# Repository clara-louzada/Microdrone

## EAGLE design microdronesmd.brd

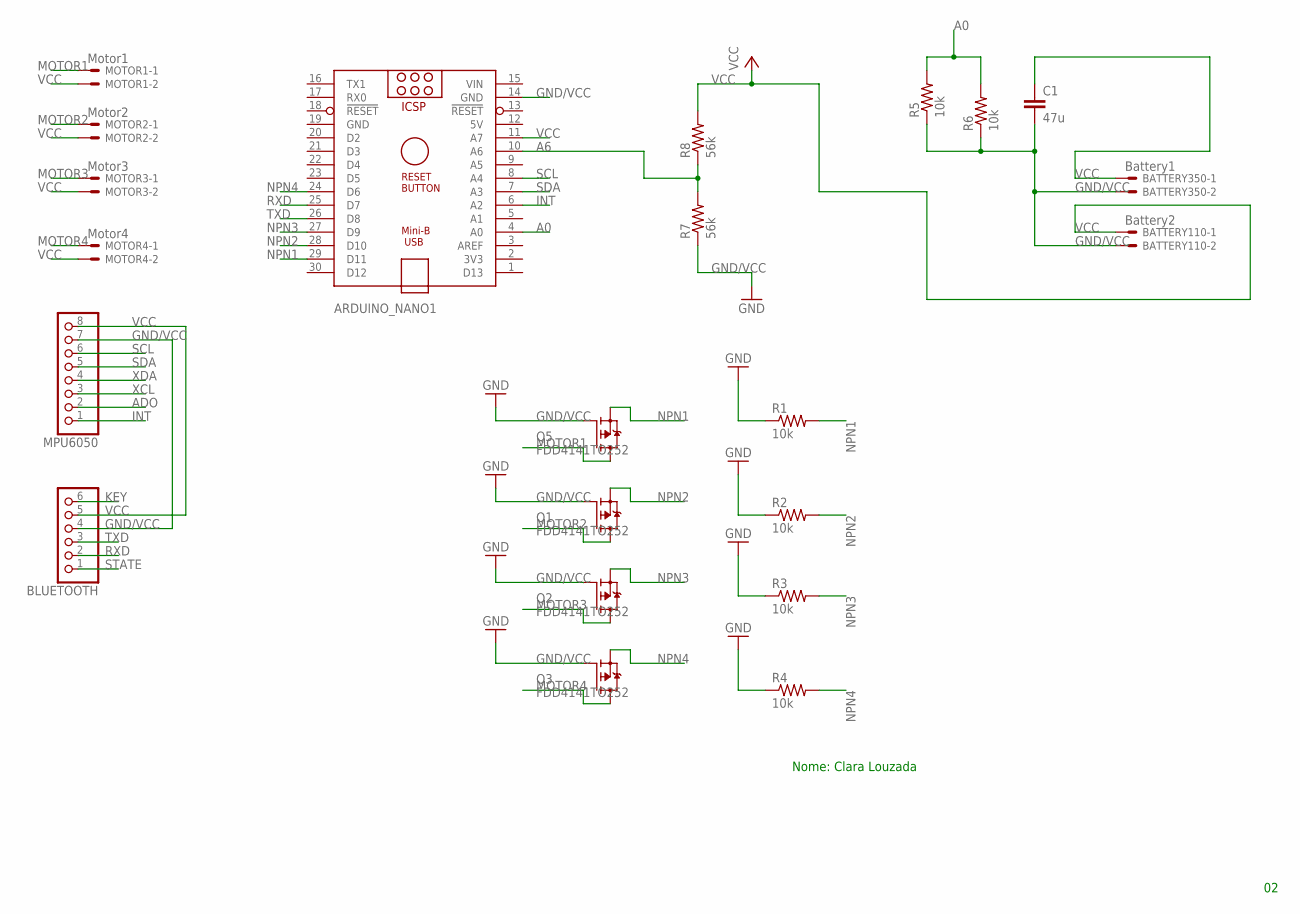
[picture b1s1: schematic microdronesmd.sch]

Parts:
ARDUINO_NANO1: ARDUINO_NANO
BATTERY110: Battery2; JST-XH-02-PACKAGE-LONG-PAD
BATTERY350: Battery1; JST-XH-02-PACKAGE-LONG-PAD
BLUETOOTH: PINHD-1X6; 1X06
C1: 47u; C2.5-3
MOTOR1: Motor1; JST-XH-02-PACKAGE-LONG-PAD
MOTOR2: Motor2; JST-XH-02-PACKAGE-LONG-PAD
MOTOR3: Motor3; JST-XH-02-PACKAGE-LONG-PAD
MOTOR4: Motor4; JST-XH-02-PACKAGE-LONG-PAD
MPU6050: PINHD-1X8; 1X08
Q1, Q2, Q3, Q5: FDD4141TO252; TO252
R1, R2, R3, R4, R5, R6: 10k; 0204/7
R7, R8: 56k; 0204/7

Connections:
5V: ARDUINO_NANO1.12 (5V)
A0: ARDUINO_NANO1.4 (A0), R5.2, R6.2
A6: ARDUINO_NANO1.10 (A6), R7.2, R8.1
ADO: MPU6050.2
GND/VCC: ARDUINO_NANO1.14 (GND), ARDUINO_NANO1.19 (GND), BATTERY110.2, BATTERY350.2, BLUETOOTH.4, C1.2, MPU6050.7, Q1.1 (G), Q2.1 (G), Q3.1 (G), Q5.1 (G), R1.1, R2.1, R3.1, R4.1, R5.1, R6.1, R7.1
INT: ARDUINO_NANO1.6 (A2), MPU6050.1
KEY: BLUETOOTH.6
MOTOR1: MOTOR1.1, Q5.3 (D)
MOTOR2: MOTOR2.1, Q1.3 (D)
MOTOR3: MOTOR3.1, Q2.3 (D)
MOTOR4: MOTOR4.1, Q3.3 (D)
NPN1: ARDUINO_NANO1.29 (D11), Q5.2 (S), R1.2
NPN2: ARDUINO_NANO1.28 (D10), Q1.2 (S), R2.2
NPN3: ARDUINO_NANO1.27 (D9), Q2.2 (S), R3.2
NPN4: ARDUINO_NANO1.24 (D6), Q3.2 (S), R4.2
RXD: ARDUINO_NANO1.25 (D7), BLUETOOTH.2
SCL: ARDUINO_NANO1.8 (A4), MPU6050.6
SDA: ARDUINO_NANO1.7 (A3), MPU6050.5
STATE: BLUETOOTH.1
TXD: ARDUINO_NANO1.26 (D8), BLUETOOTH.3
VCC: ARDUINO_NANO1.11 (A7), BATTERY110.1, BATTERY350.1, BLUETOOTH.5, C1.1, MOTOR1.2, MOTOR2.2, MOTOR3.2, MOTOR4.2, MPU6050.8, R8.2
VIN: ARDUINO_NANO1.15 (VIN)
XCL: MPU6050.3
XDA: MPU6050.4

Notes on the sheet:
Nome: Clara Louzada

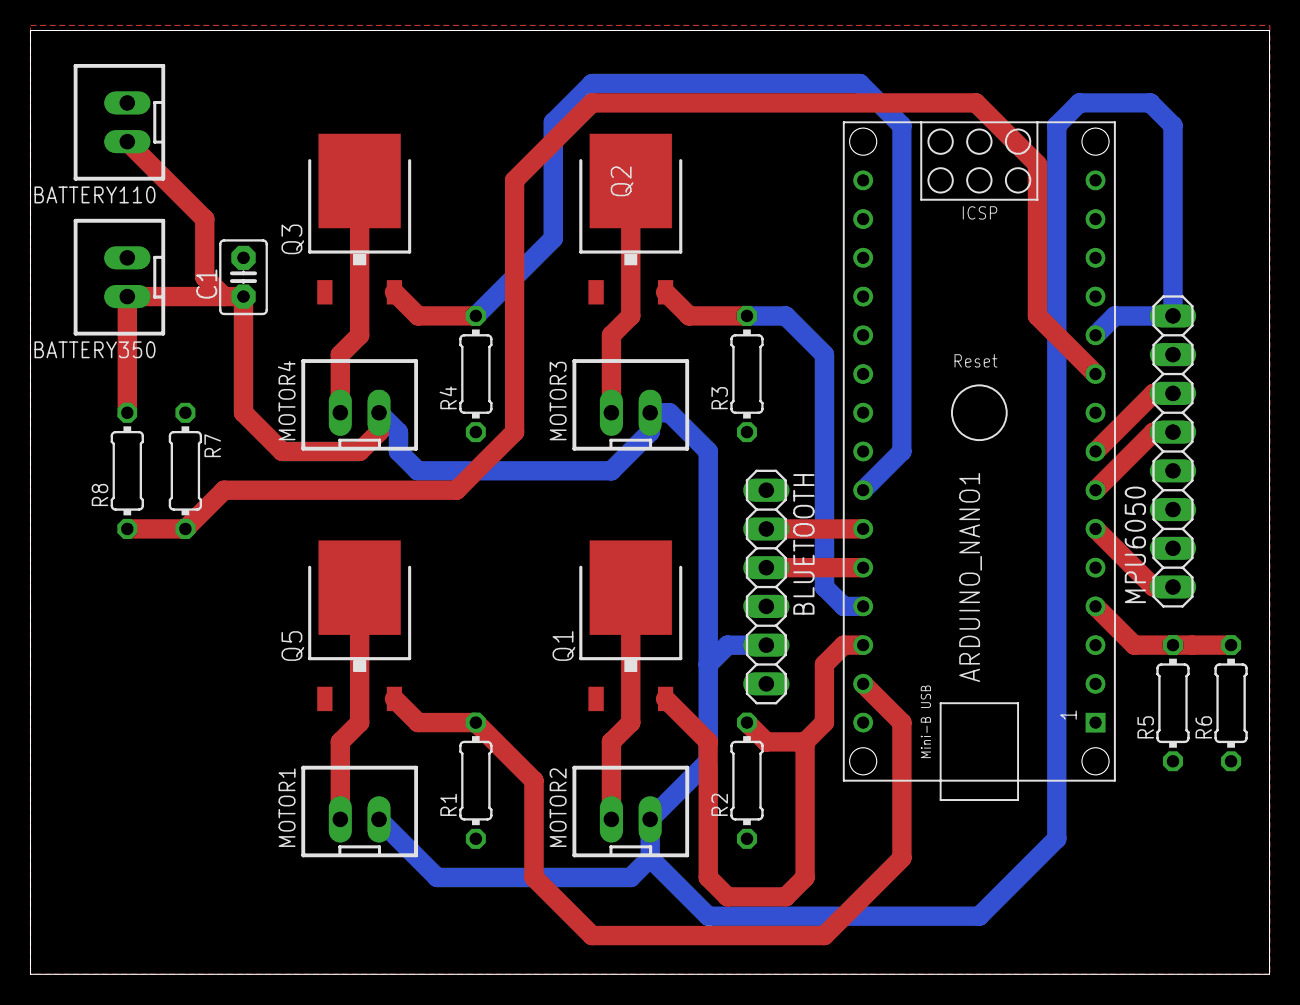
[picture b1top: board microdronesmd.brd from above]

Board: 2 copper layers, 81.3 x 61.9 mm, 22 parts (0 on the bottom side), 17 nets.

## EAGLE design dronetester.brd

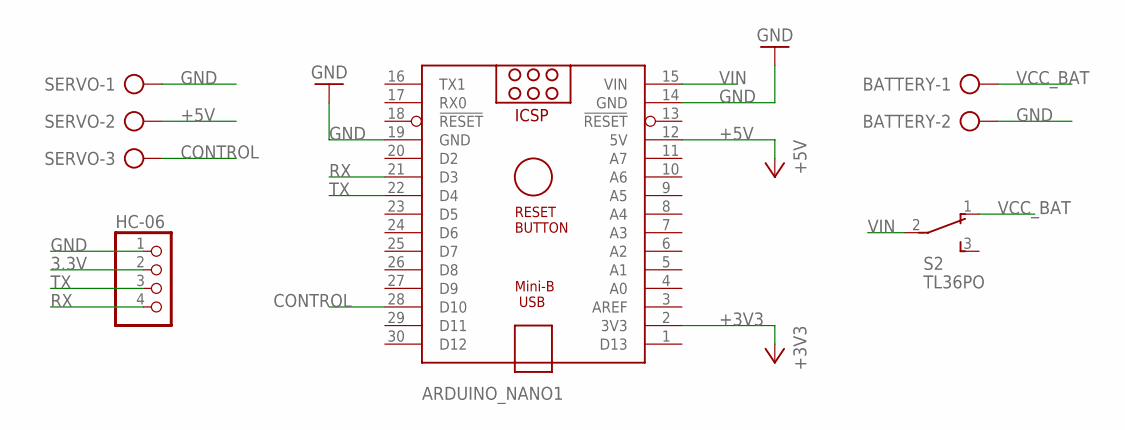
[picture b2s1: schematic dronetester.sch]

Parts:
ARDUINO_NANO1: ARDUINO_NANO
BATTERY: AK500/2-H
HC-06: PINHD-1X4; 1X04
S2: TL36PO; TL3XPO
SERVO: AK500/3-H

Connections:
3.3V: HC-06.2
+3V3: ARDUINO_NANO1.2 (3V3)
+5V: ARDUINO_NANO1.12 (5V), SERVO.2
CONTROL: ARDUINO_NANO1.28 (D10), SERVO.3
GND: ARDUINO_NANO1.14 (GND), ARDUINO_NANO1.19 (GND), BATTERY.2, HC-06.1, SERVO.1
RX: ARDUINO_NANO1.21 (D3), HC-06.4
TX: ARDUINO_NANO1.22 (D4), HC-06.3
VCC_BAT: BATTERY.1, S2.1 (O)
VIN: ARDUINO_NANO1.15 (VIN), S2.2

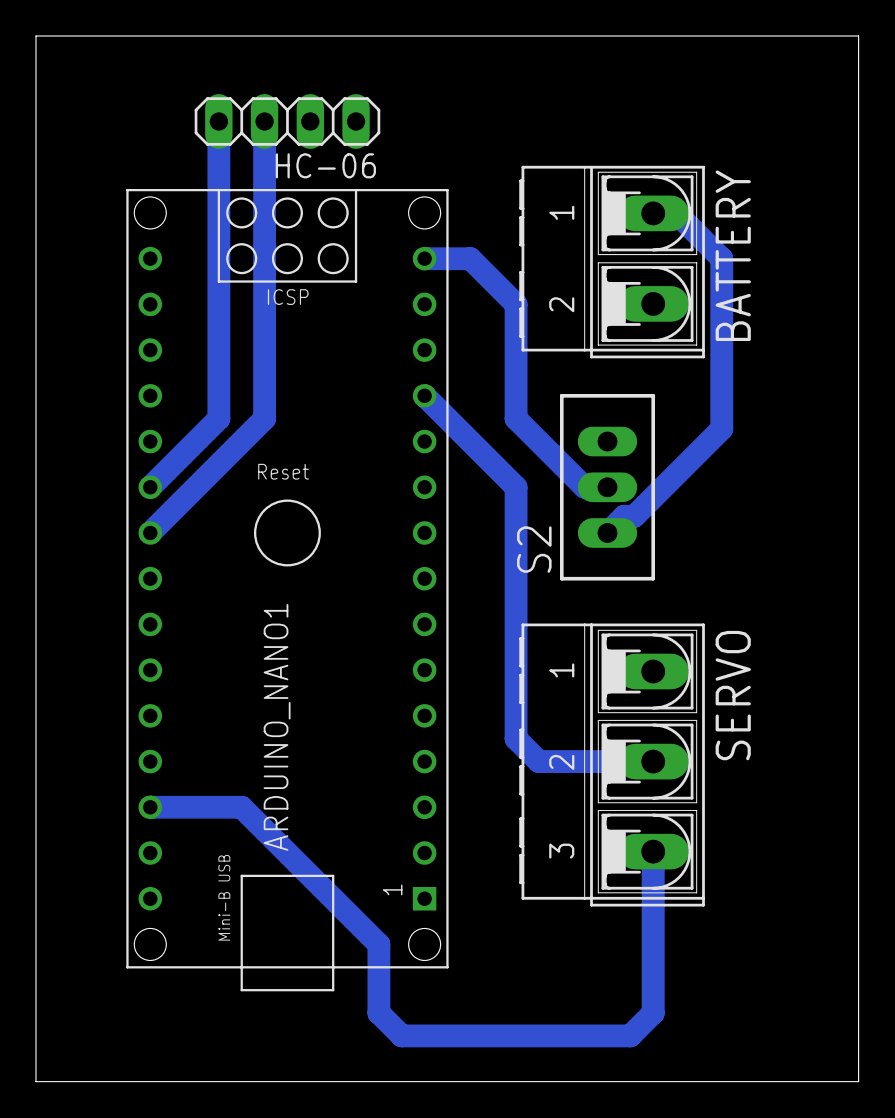
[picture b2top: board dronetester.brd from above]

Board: 2 copper layers, 45.7 x 58.1 mm, 5 parts (0 on the bottom side), 7 nets.

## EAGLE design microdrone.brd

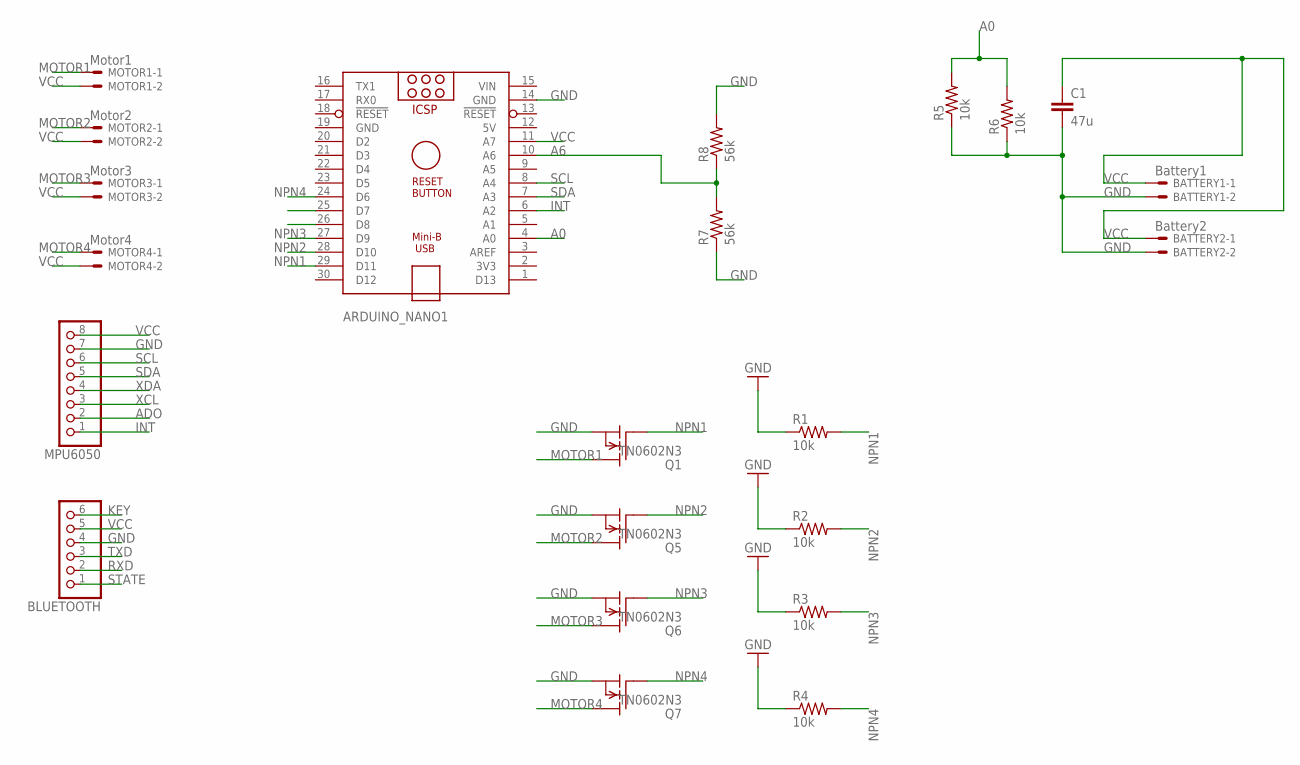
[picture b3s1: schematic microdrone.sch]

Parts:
ARDUINO_NANO1: ARDUINO_NANO
BATTERY1: Battery1; JST-XH-02-PACKAGE-LONG-PAD
BATTERY2: Battery2; JST-XH-02-PACKAGE-LONG-PAD
BLUETOOTH: PINHD-1X6; 1X06
C1: 47u; C2.5-3
MOTOR1: Motor1; JST-XH-02-PACKAGE-LONG-PAD
MOTOR2: Motor2; JST-XH-02-PACKAGE-LONG-PAD
MOTOR3: Motor3; JST-XH-02-PACKAGE-LONG-PAD
MOTOR4: Motor4; JST-XH-02-PACKAGE-LONG-PAD
MPU6050: PINHD-1X8; 1X08
Q1, Q5, Q6, Q7: TN0602N3; TO-92
R1, R2, R3, R4, R5, R6: 10k; 0204/7
R7, R8: 56k; 0204/7

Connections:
5V: ARDUINO_NANO1.12 (5V)
A0: ARDUINO_NANO1.4 (A0), R5.2, R6.2
A6: ARDUINO_NANO1.10 (A6), R7.2, R8.1
ADO: MPU6050.2
GND: ARDUINO_NANO1.14 (GND), ARDUINO_NANO1.19 (GND), BATTERY1.2, BATTERY2.2, BLUETOOTH.4, C1.2, MPU6050.7, Q1.1 (S), Q5.1 (S), Q6.1 (S), Q7.1 (S), R1.1, R2.1, R3.1, R4.1, R5.1, R6.1, R7.1, R8.2
INT: ARDUINO_NANO1.6 (A2), MPU6050.1
KEY: BLUETOOTH.6
MOTOR1: MOTOR1.1, Q1.3 (D)
MOTOR2: MOTOR2.1, Q5.3 (D)
MOTOR3: MOTOR3.1, Q6.3 (D)
MOTOR4: MOTOR4.1, Q7.3 (D)
NPN1: ARDUINO_NANO1.29 (D11), Q1.2 (G), R1.2
NPN2: ARDUINO_NANO1.28 (D10), Q5.2 (G), R2.2
NPN3: ARDUINO_NANO1.27 (D9), Q6.2 (G), R3.2
NPN4: ARDUINO_NANO1.24 (D6), Q7.2 (G), R4.2
RXD: BLUETOOTH.2
SCL: ARDUINO_NANO1.8 (A4), MPU6050.6
SDA: ARDUINO_NANO1.7 (A3), MPU6050.5
STATE: BLUETOOTH.1
TXD: BLUETOOTH.3
VCC: ARDUINO_NANO1.11 (A7), BATTERY1.1, BATTERY2.1, BLUETOOTH.5, C1.1, MOTOR1.2, MOTOR2.2, MOTOR3.2, MOTOR4.2, MPU6050.8
VIN: ARDUINO_NANO1.15 (VIN)
XCL: MPU6050.3
XDA: MPU6050.4

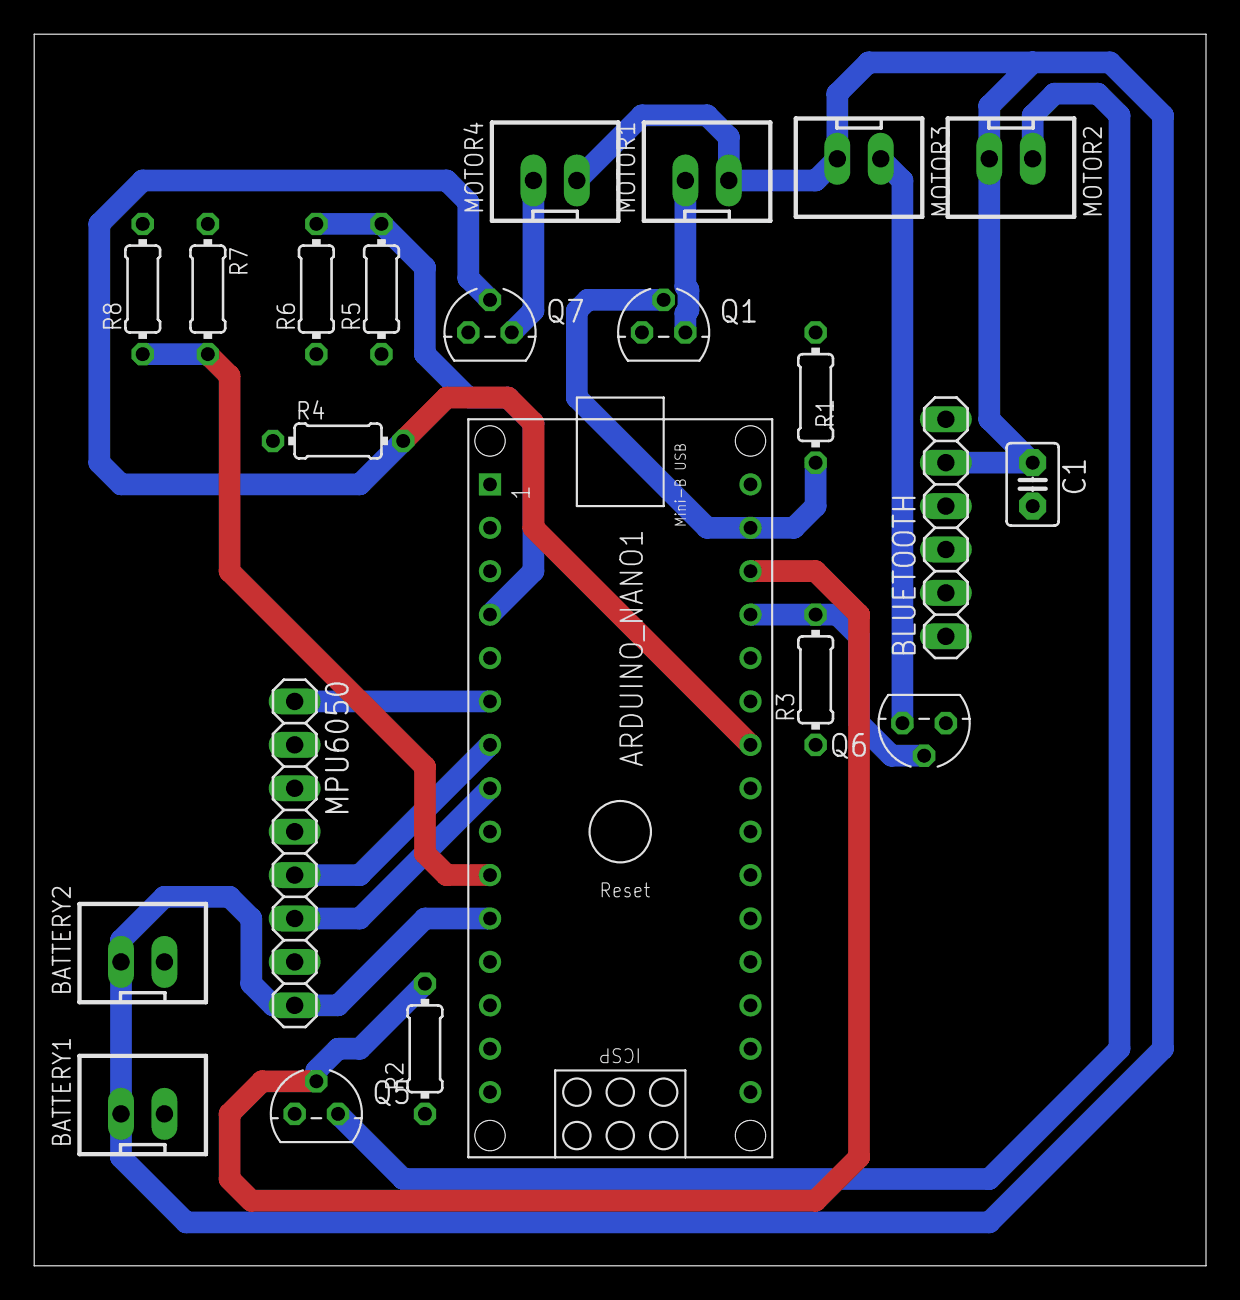
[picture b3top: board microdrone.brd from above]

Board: 2 copper layers, 68.6 x 72.1 mm, 22 parts (0 on the bottom side), 15 nets.

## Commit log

2019-04-19 Second commit
